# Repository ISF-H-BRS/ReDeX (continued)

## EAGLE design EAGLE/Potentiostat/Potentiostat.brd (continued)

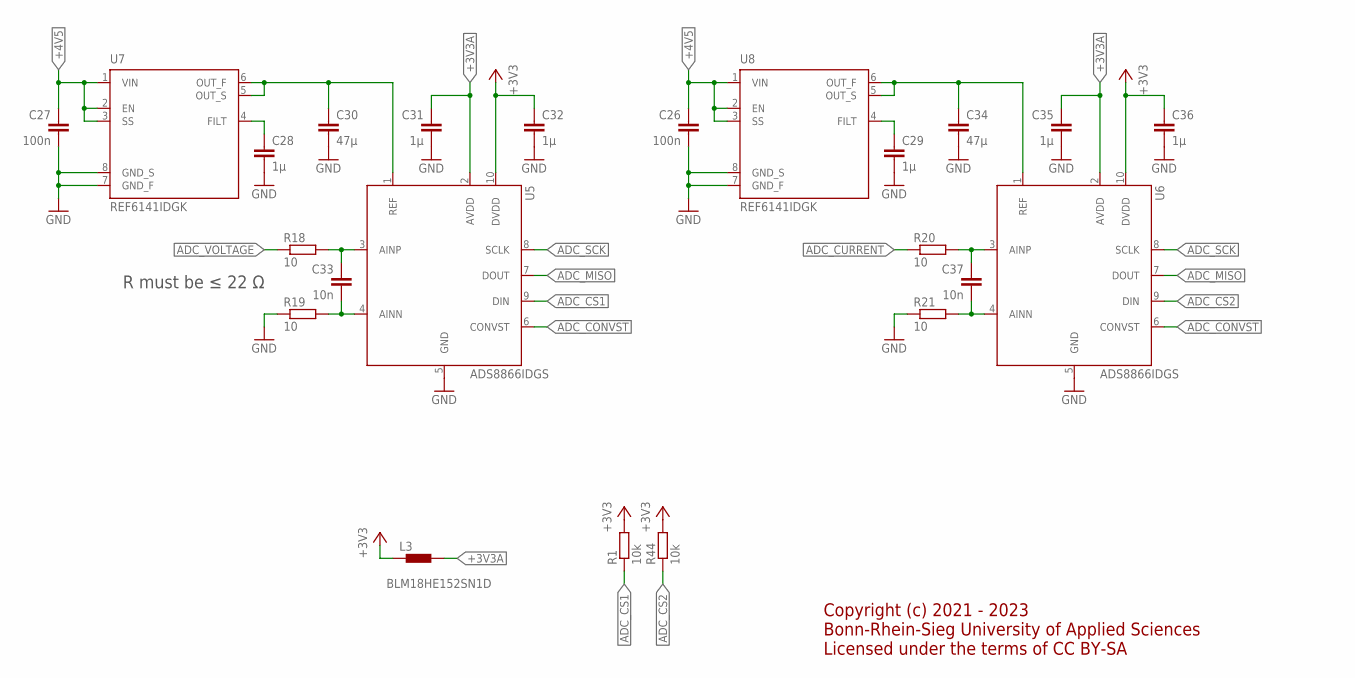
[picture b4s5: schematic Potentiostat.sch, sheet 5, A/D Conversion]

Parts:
C26, C27: 100n; C0603
C28, C29, C31, C32, C35, C36: 1µ; C0603
C30, C34: 47µ; C0805
C33, C37: 10n; C0603
L3: BLM18HE152SN1D; 0603
R1, R44: 10k; R0603
R18, R19, R20, R21: 10; R0603
U5, U6: ADS8866IDGS; MSOP10
U7, U8: REF6141IDGK; VSSOP8

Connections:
+3V3: C32.1, C36.1, L3.2, R1.2, R44.2, U5.10 (DVDD), U6.10 (DVDD); also elsewhere on the board
+3V3A: C31.1, C35.1, L3.1, U5.2 (AVDD), U6.2 (AVDD)
+4V5: C26.1, C27.1, U7.1 (VIN), U7.2 (EN), U7.3 (SS), U8.1 (VIN), U8.2 (EN), U8.3 (SS); also elsewhere on the board
ADC_CONVST: U5.6 (CONVST), U6.6 (CONVST); also elsewhere on the board
ADC_CS1: R1.1, U5.9 (DIN); also elsewhere on the board
ADC_CS2: R44.1, U6.9 (DIN); also elsewhere on the board
ADC_CURRENT: R20.1; also elsewhere on the board
ADC_MISO: U5.7 (DOUT), U6.7 (DOUT); also elsewhere on the board
ADC_SCK: U5.8 (SCLK), U6.8 (SCLK); also elsewhere on the board
ADC_VOLTAGE: R18.1; also elsewhere on the board
GND: C26.2, C27.2, C28.2, C29.2, C30.2, C31.2, C32.2, C34.2, C35.2, C36.2, R19.1, R21.1, U5.5 (GND), U6.5 (GND), U7.7 (GND_F), U7.8 (GND_S), U8.7 (GND_F), U8.8 (GND_S); also elsewhere on the board
unnamed: C28.1, U7.4 (FILT)
unnamed: C30.1, U5.1 (REF), U7.5 (OUT_S), U7.6 (OUT_F)
unnamed: C33.1, R18.2, U5.3 (AINP)
unnamed: C29.1, U8.4 (FILT)
unnamed: C34.1, U6.1 (REF), U8.5 (OUT_S), U8.6 (OUT_F)
unnamed: C33.2, R19.2, U5.4 (AINN)
unnamed: C37.1, R20.2, U6.3 (AINP)
unnamed: C37.2, R21.2, U6.4 (AINN)

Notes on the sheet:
R must be ≤ 22 Ω
Copyright (c) 2021 - 2023 Bonn-Rhein-Sieg University of Applied Sciences Licensed under the terms of CC BY-SA

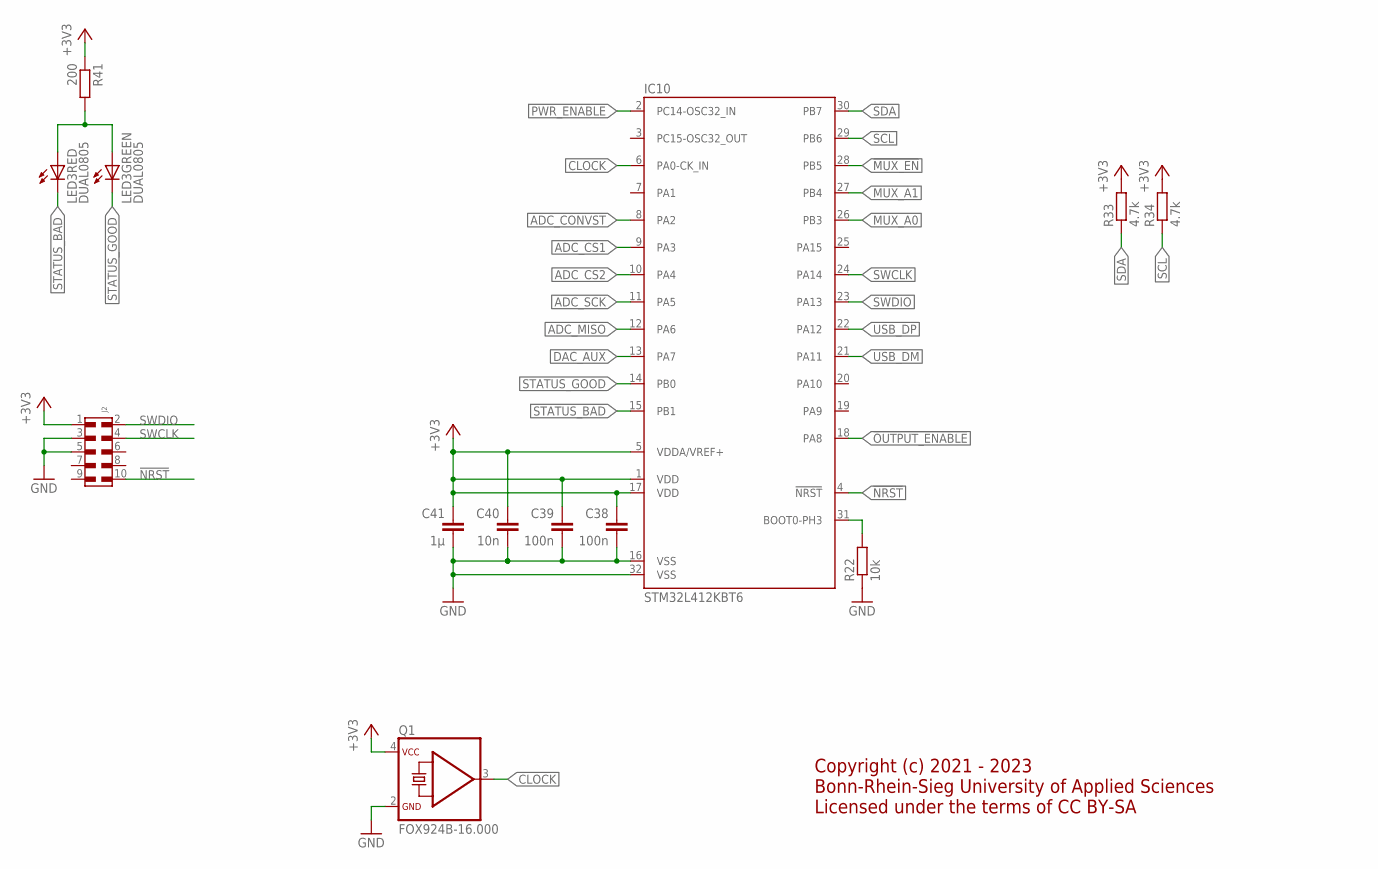
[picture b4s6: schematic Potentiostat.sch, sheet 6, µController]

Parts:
C38, C39: 100n; C0603
C40: 10n; C0603
C41: 1µ; C0603
IC10: STM32L412KBT6; LQFP32
J2: 6210XX21021_62101021021; 62101021021
LED3: DUAL0805; CHIPLEDX2
Q1: FOX924B-16.000; FOX924B
R22: 10k; R0603
R33, R34: 4.7k; R0603
R41: 200; R0603

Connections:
!MUX_EN: IC10.28 (PB5); also elsewhere on the board
!NRST: IC10.4 (!NRST), J2.10
!OUTPUT_ENABLE: IC10.18 (PA8); also elsewhere on the board
+3V3: C38.1, C39.1, C40.1, C41.1, IC10.1 (VDD), IC10.5 (VDDA/VREF+), IC10.17 (VDD), J2.1, Q1.4 (VCC), R33.2, R34.2, R41.1; also elsewhere on the board
ADC_CONVST: IC10.8 (PA2); also elsewhere on the board
ADC_CS1: IC10.9 (PA3); also elsewhere on the board
ADC_CS2: IC10.10 (PA4); also elsewhere on the board
ADC_MISO: IC10.12 (PA6); also elsewhere on the board
ADC_SCK: IC10.11 (PA5); also elsewhere on the board
CLOCK: IC10.6 (PA0-CK_IN), Q1.3 (OUT)
DAC_AUX: IC10.13 (PA7); also elsewhere on the board
GND: C38.2, C39.2, C40.2, C41.2, IC10.16 (VSS), IC10.32 (VSS), J2.3, J2.5, Q1.2 (GND), R22.1; also elsewhere on the board
MUX_A0: IC10.26 (PB3); also elsewhere on the board
MUX_A1: IC10.27 (PB4); also elsewhere on the board
unnamed: IC10.31 (BOOT0-PH3), R22.2
unnamed: LED3.A1 (A), LED3.A2 (A), R41.2
PWR_ENABLE: IC10.2 (PC14-OSC32_IN); also elsewhere on the board
SCL: IC10.29 (PB6), R34.1; also elsewhere on the board
SDA: IC10.30 (PB7), R33.1; also elsewhere on the board
STATUS_BAD: IC10.15 (PB1), LED3.C1 (C)
STATUS_GOOD: IC10.14 (PB0), LED3.C2 (C)
SWCLK: IC10.24 (PA14), J2.4
SWDIO: IC10.23 (PA13), J2.2
USB_DM: IC10.21 (PA11); also elsewhere on the board
USB_DP: IC10.22 (PA12); also elsewhere on the board

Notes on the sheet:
Copyright (c) 2021 - 2023 Bonn-Rhein-Sieg University of Applied Sciences Licensed under the terms of CC BY-SA

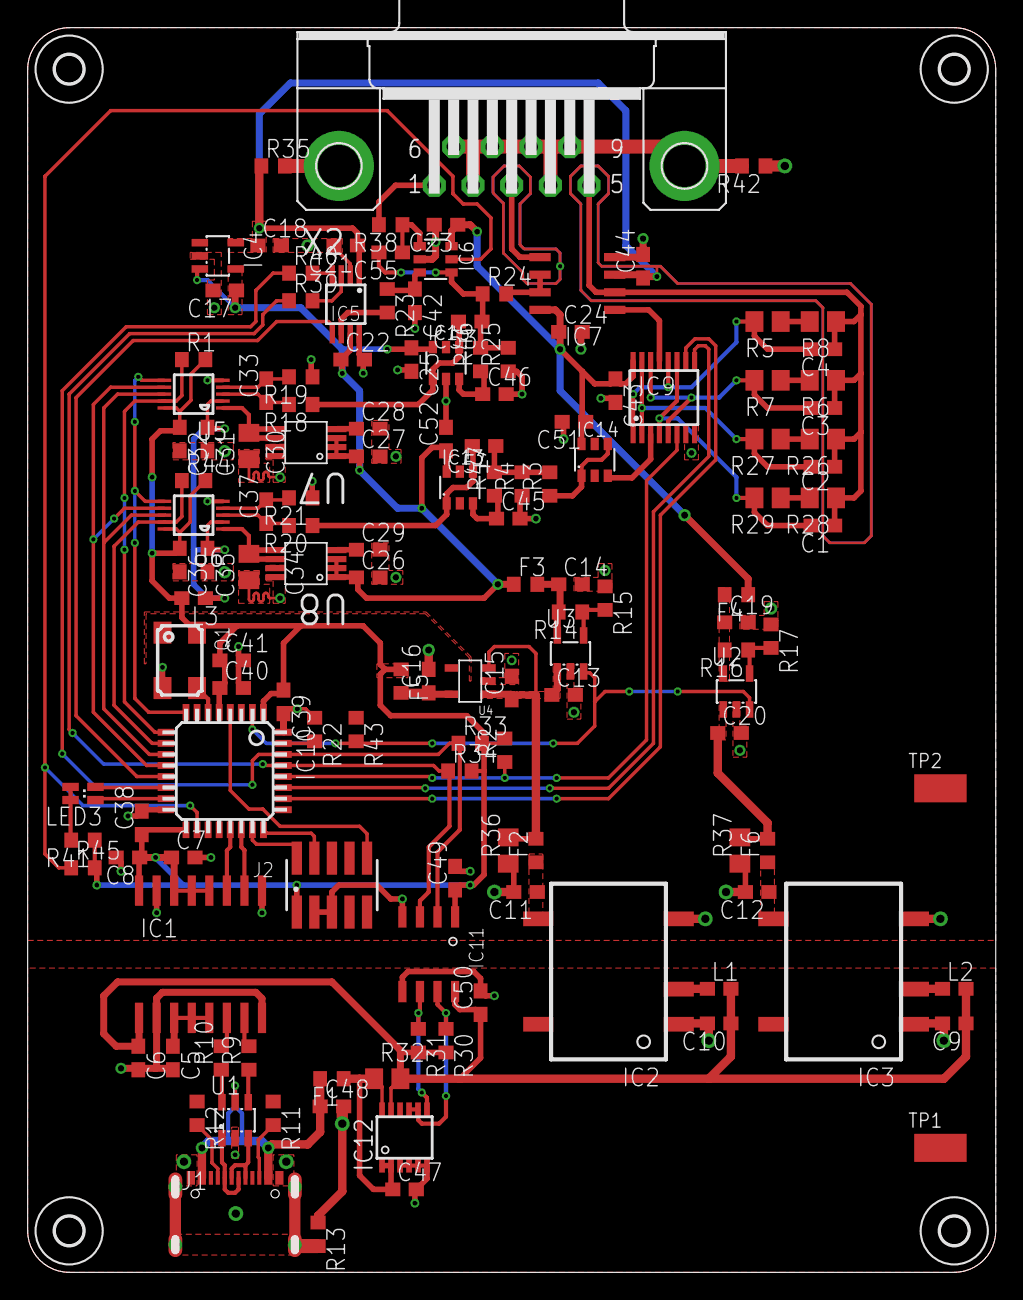
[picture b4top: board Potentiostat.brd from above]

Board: 2 copper layers, 69.4 x 89.4 mm, 144 parts (0 on the bottom side), 92 nets.

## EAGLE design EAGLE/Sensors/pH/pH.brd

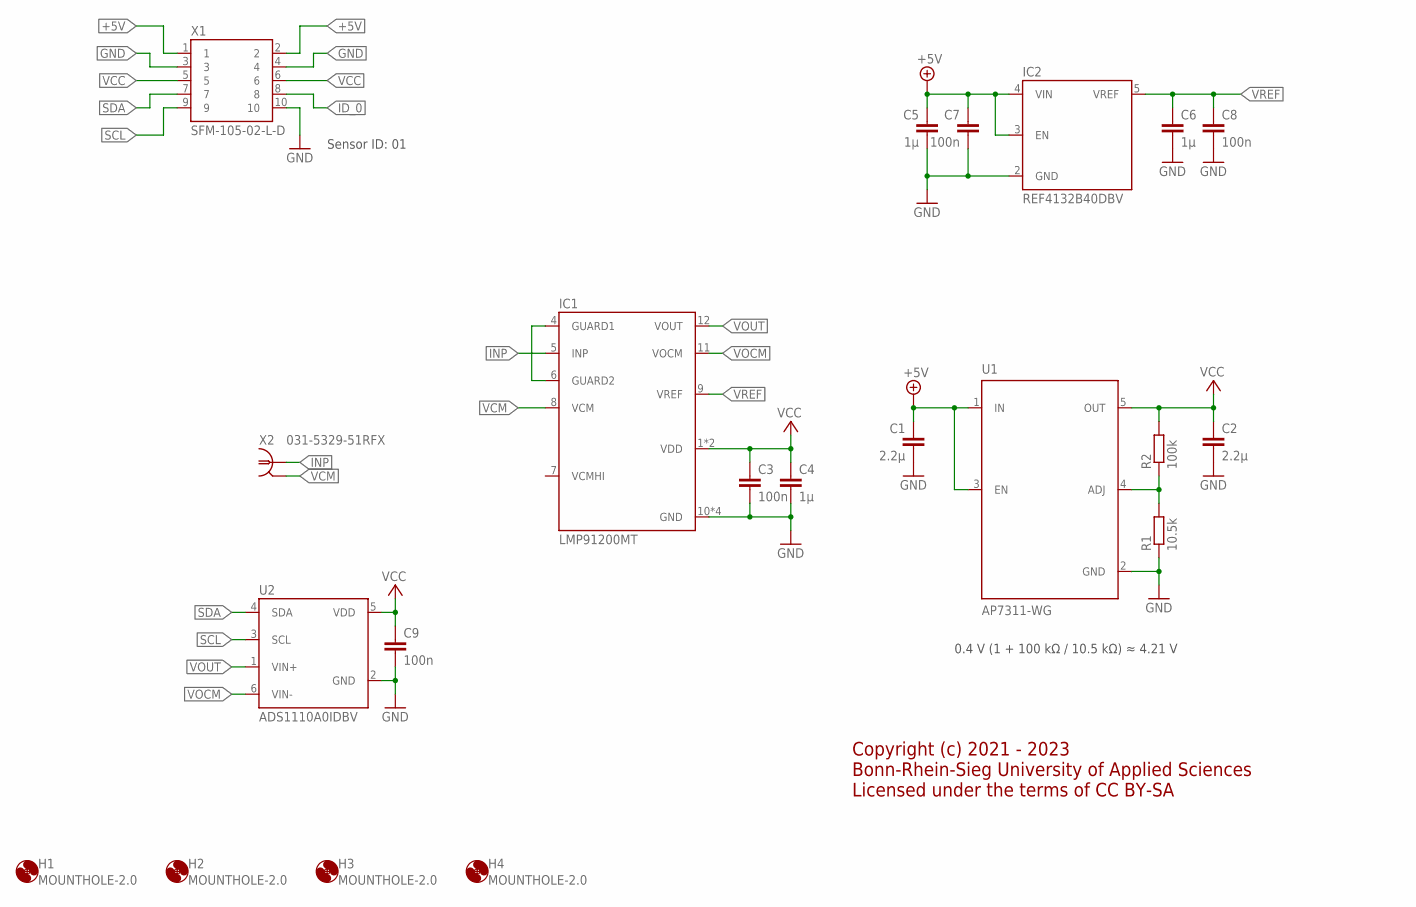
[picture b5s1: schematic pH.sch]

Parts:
C1, C2: 2.2µ; C0603
C3, C7, C8, C9: 100n; C0603
C4, C5, C6: 1µ; C0603
H1, H2, H3, H4: MOUNTHOLE-2.0; 2.0
IC1: LMP91200MT; TSSOP16
IC2: REF4132B40DBV; SOT23-5
R1: 10.5k; R0603
R2: 100k; R0603
U1: AP7311-WG; SOT-23
U2: ADS1110A0IDBV; SOT23-6
X1: SFM-105-02-L-D; SAMTEC-SFM-105-02-L-D
X2: 031-5329-51RFX

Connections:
+5V: C1.1, C5.1, C7.1, IC2.3 (EN), IC2.4 (VIN), U1.1 (IN), U1.3 (EN), X1.1, X1.2
GND: C1.2, C2.2, C3.2, C4.2, C5.2, C6.2, C7.2, C8.2, C9.2, IC1.10 (GND), IC1.13 (GND), IC1.15 (GND), IC1.16 (GND), IC2.2 (GND), R1.1, U1.2 (GND), U2.2 (GND), X1.3, X1.4, X1.10
ID_0: X1.8
INP: IC1.5 (INP), X2.1
unnamed: IC1.4 (GUARD1), IC1.6 (GUARD2)
unnamed: R1.2, R2.1, U1.4 (ADJ)
SCL: U2.3 (SCL), X1.9
SDA: U2.4 (SDA), X1.7
VCC: C2.1, C3.1, C4.1, C9.1, IC1.1 (VDD), IC1.14 (VDD), R2.2, U1.5 (OUT), U2.5 (VDD), X1.5, X1.6
VCM: IC1.8 (VCM), X2.2, X2.3 (2), X2.4 (2), X2.5 (2)
VOCM: IC1.11 (VOCM), U2.6 (VIN-)
VOUT: IC1.12 (VOUT), U2.1 (VIN+)
VREF: C6.1, C8.1, IC1.9 (VREF), IC2.5 (VREF)

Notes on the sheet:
0.4 V (1 + 100 kΩ / 10.5 kΩ) ≈ 4.21 V
Sensor ID: 01
Copyright (c) 2021 - 2023 Bonn-Rhein-Sieg University of Applied Sciences Licensed under the terms of CC BY-SA

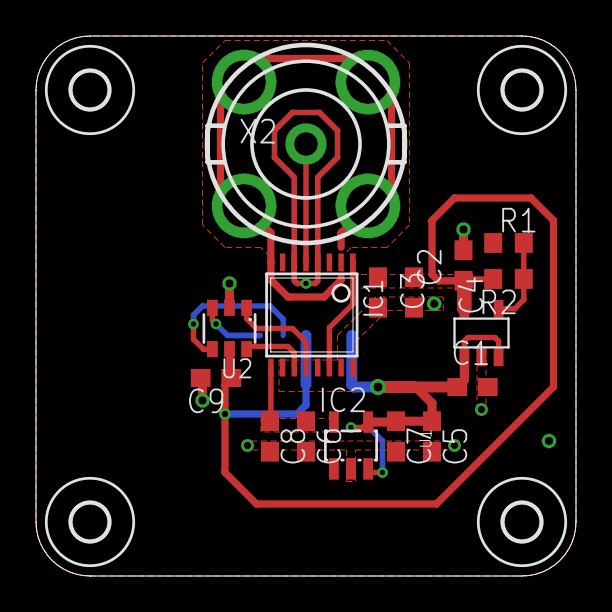
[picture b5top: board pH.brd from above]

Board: 2 copper layers, 30.0 x 30.0 mm, 21 parts (1 on the bottom side), 12 nets.

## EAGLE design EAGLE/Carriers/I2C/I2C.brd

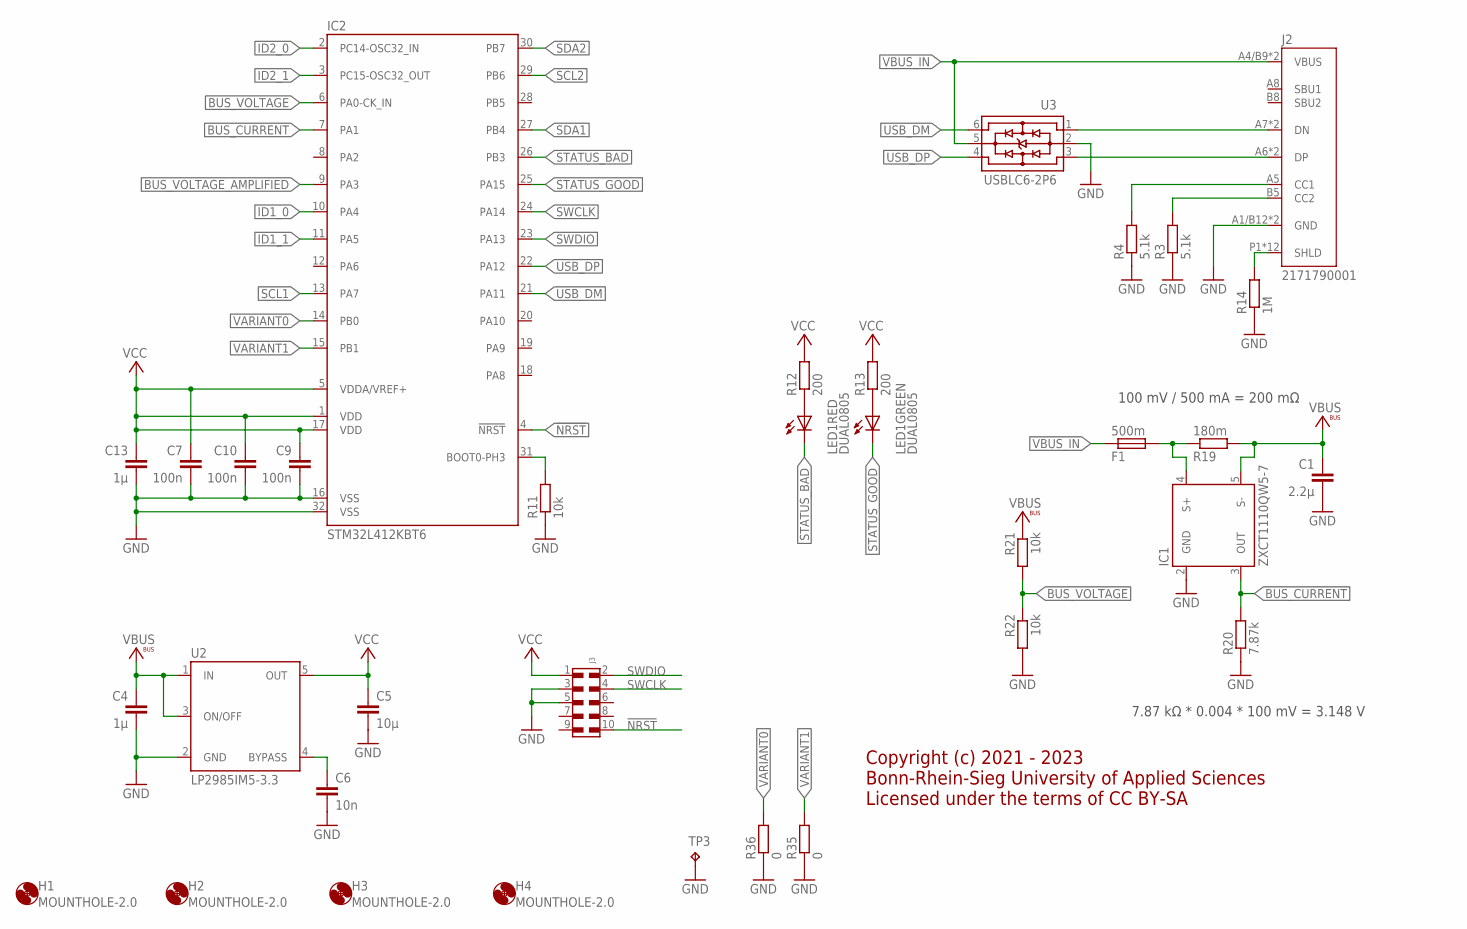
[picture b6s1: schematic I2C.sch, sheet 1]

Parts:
C1: 2.2µ; C0805
C4: 1µ; C0805
C5: 10µ; C0603
C6: 10n; C0603
C7, C9, C10: 100n; C0603
C13: 1µ; C0603
F1: 500m; R0603
H1, H2, H3, H4: MOUNTHOLE-2.0; 2.0
IC1: ZXCT1110QW5-7; SOT23-5L
IC2: STM32L412KBT6; LQFP32
J2: 2171790001; 2171790001_MOL
J3: 6210XX21021_62101021021; 62101021021
LED1: DUAL0805; CHIPLEDX2
R3, R4: 5.1k; R0603
R11, R21, R22: 10k; R0603
R12, R13: 200; R0603
R14: 1M; R0603
R19: 180m; R0805
R20: 7.87k; R0603
R35, R36: 0; R0603
TP3: TP3.8X2.03; 3.8X2.03
U2: LP2985IM5-3.3; SOT23-5
U3: USBLC6-2P6; SOT-666

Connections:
!NRST: IC2.4 (!NRST), J3.10
BUS_CURRENT: IC1.3 (OUT), IC2.7 (PA1), R20.2
BUS_VOLTAGE: IC2.6 (PA0-CK_IN), R21.2, R22.1
BUS_VOLTAGE_AMPLIFIED: IC2.9 (PA3)
GND: C1.2, C4.2, C5.2, C6.2, C7.2, C9.2, C10.2, C13.2, IC1.2 (GND), IC2.16 (VSS), IC2.32 (VSS), J2.A1/B12 (GND), J2.B1/A12 (GND), J3.3, J3.5, R3.1, R4.1, R11.1, R14.1, R20.1, R22.2, R35.1, R36.1, TP3.TP, U2.2 (GND), U3.2; also elsewhere on the board
ID1_0: IC2.10 (PA4); also elsewhere on the board
ID1_1: IC2.11 (PA5); also elsewhere on the board
ID2_0: IC2.2 (PC14-OSC32_IN); also elsewhere on the board
ID2_1: IC2.3 (PC15-OSC32_OUT); also elsewhere on the board
unnamed: J2.P1 (SHLD), J2.P2 (SHLD), J2.P3 (SHLD), J2.P4 (SHLD), J2.S1 (SHLD), J2.S2 (SHLD), J2.S3 (SHLD), J2.S4 (SHLD), J2.S5 (SHLD), J2.S6 (SHLD), J2.S7 (SHLD), J2.S8 (SHLD), R14.2
unnamed: J2.A6 (DP), J2.B6 (DP), U3.3
unnamed: J2.A7 (DN), J2.B7 (DN), U3.1
unnamed: J2.B5 (CC2), R3.2
unnamed: J2.A5 (CC1), R4.2
unnamed: C6.1, U2.4 (BYPASS)
unnamed: IC2.31 (BOOT0-PH3), R11.2
unnamed: LED1.A2 (A), R13.1
unnamed: LED1.A1 (A), R12.1
unnamed: F1.2, IC1.4 (S+), R19.1
SCL1: IC2.13 (PA7); also elsewhere on the board
SCL2: IC2.29 (PB6); also elsewhere on the board
SDA1: IC2.27 (PB4); also elsewhere on the board
SDA2: IC2.30 (PB7); also elsewhere on the board
STATUS_BAD: IC2.26 (PB3), LED1.C1 (C)
STATUS_GOOD: IC2.25 (PA15), LED1.C2 (C)
SWCLK: IC2.24 (PA14), J3.4
SWDIO: IC2.23 (PA13), J3.2
USB_DM: IC2.21 (PA11), U3.6
USB_DP: IC2.22 (PA12), U3.4
VARIANT0: IC2.14 (PB0), R36.2
VARIANT1: IC2.15 (PB1), R35.2
VBUS: C1.1, C4.1, IC1.5 (S-), R19.2, R21.1, U2.1 (IN), U2.3 (ON/OFF); also elsewhere on the board
VBUS_IN: F1.1, J2.A4/B9 (VBUS), J2.B4/A9 (VBUS), U3.5
VCC: C5.1, C7.1, C9.1, C10.1, C13.1, IC2.1 (VDD), IC2.5 (VDDA/VREF+), IC2.17 (VDD), J3.1, R12.2, R13.2, U2.5 (OUT); also elsewhere on the board

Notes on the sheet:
100 mV / 500 mA = 200 mΩ
7.87 kΩ * 0.004 * 100 mV = 3.148 V
Copyright (c) 2021 - 2023 Bonn-Rhein-Sieg University of Applied Sciences Licensed under the terms of CC BY-SA

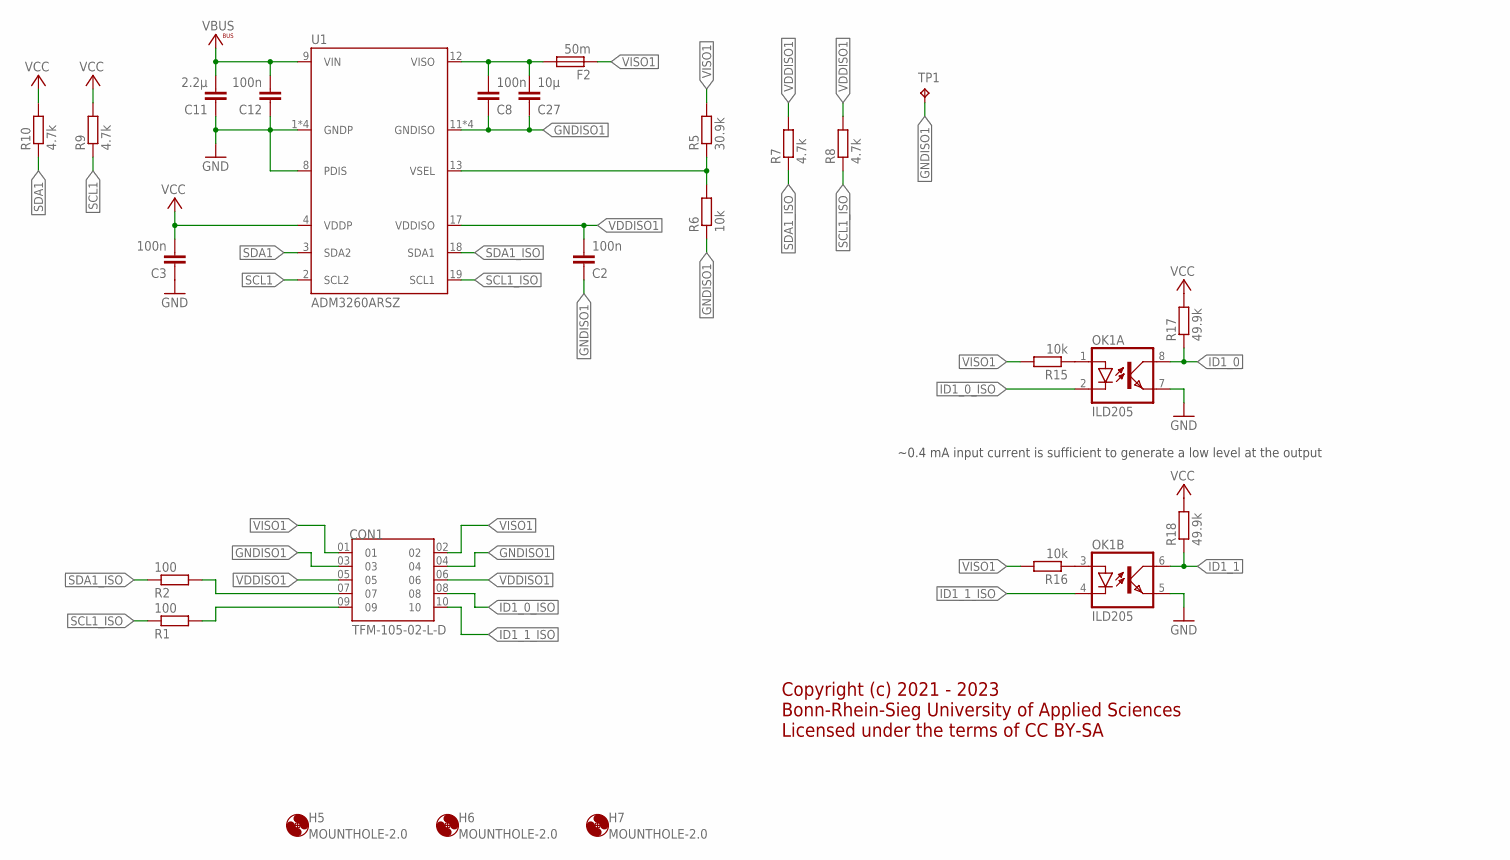
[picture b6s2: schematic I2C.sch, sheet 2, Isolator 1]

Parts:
C2, C3, C8, C12: 100n; C0603
C11: 2.2µ; C0603
C27: 10µ; C0603
CON1: TFM-105-02-L-D; SAMTEC_TFM-105-02-L-D
F2: 50m; R0603
H5, H6, H7: MOUNTHOLE-2.0; 2.0
OK1: ILD205; SOIC08
R1, R2: 100; R0603
R5: 30.9k; R0603
R6, R15, R16: 10k; R0603
R7, R8, R9, R10: 4.7k; R0603
R17, R18: 49.9k; R0603
TP1: TP3.8X2.03; 3.8X2.03
U1: ADM3260ARSZ; SSOP20

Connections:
GND: C3.1, C11.1, C12.1, OK1.5 (EMIT), OK1.7 (EMIT), U1.1 (GNDP), U1.5 (GNDP), U1.7 (GNDP), U1.8 (PDIS), U1.10 (GNDP); also elsewhere on the board
GNDISO1: C2.1, C8.1, C27.1, CON1.03, CON1.04, R6.1, TP1.TP, U1.11 (GNDISO), U1.14 (GNDISO), U1.16 (GNDISO), U1.20 (GNDISO)
ID1_0: OK1.8 (COL), R17.1; also elsewhere on the board
ID1_0_ISO: CON1.08, OK1.2 (C)
ID1_1: OK1.6 (COL), R18.1; also elsewhere on the board
ID1_1_ISO: CON1.10, OK1.4 (C)
unnamed: CON1.09, R1.2
unnamed: R5.1, R6.2, U1.13 (VSEL)
unnamed: CON1.07, R2.2
unnamed: OK1.3 (A), R16.1
unnamed: OK1.1 (A), R15.1
unnamed: C8.2, C27.2, F2.2, U1.12 (VISO)
SCL1: R9.1, U1.2 (SCL2); also elsewhere on the board
SCL1_ISO: R1.1, R8.1, U1.19 (SCL1)
SDA1: R10.1, U1.3 (SDA2); also elsewhere on the board
SDA1_ISO: R2.1, R7.1, U1.18 (SDA1)
VBUS: C11.2, C12.2, U1.9 (VIN); also elsewhere on the board
VCC: C3.2, R9.2, R10.2, R17.2, R18.2, U1.4 (VDDP); also elsewhere on the board
VDDISO1: C2.2, CON1.05, CON1.06, R7.2, R8.2, U1.17 (VDDISO)
VISO1: CON1.01, CON1.02, F2.1, R5.2, R15.2, R16.2

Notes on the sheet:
~0.4 mA input current is sufficient to generate a low level at the output
Copyright (c) 2021 - 2023 Bonn-Rhein-Sieg University of Applied Sciences Licensed under the terms of CC BY-SA

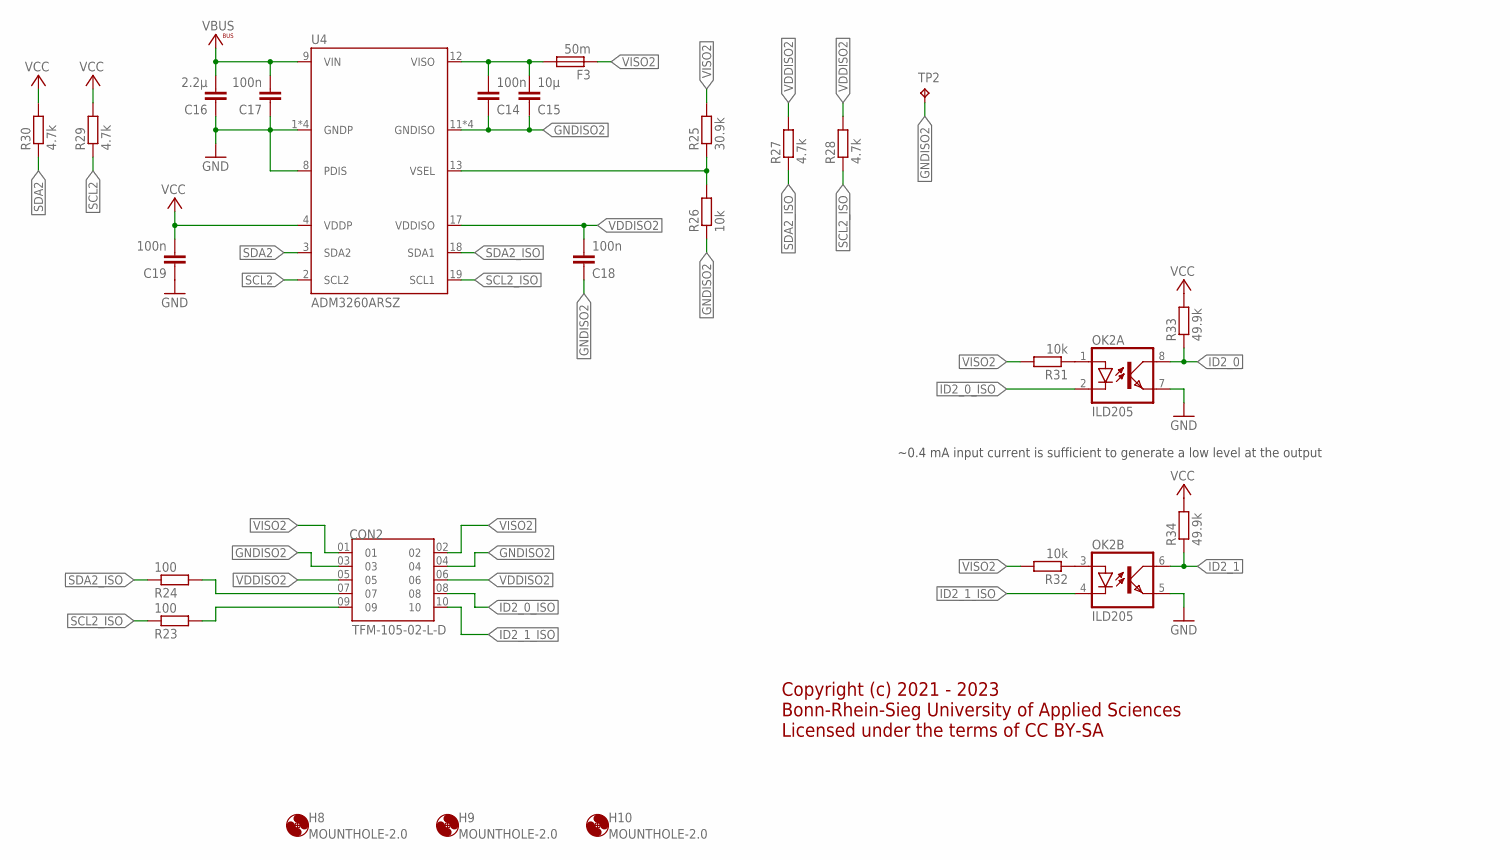
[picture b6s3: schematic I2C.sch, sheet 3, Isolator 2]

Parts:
C14, C17, C18, C19: 100n; C0603
C15: 10µ; C0603
C16: 2.2µ; C0603
CON2: TFM-105-02-L-D; SAMTEC_TFM-105-02-L-D
F3: 50m; R0603
H8, H9, H10: MOUNTHOLE-2.0; 2.0
OK2: ILD205; SOIC08
R23, R24: 100; R0603
R25: 30.9k; R0603
R26, R31, R32: 10k; R0603
R27, R28, R29, R30: 4.7k; R0603
R33, R34: 49.9k; R0603
TP2: TP3.8X2.03; 3.8X2.03
U4: ADM3260ARSZ; SSOP20

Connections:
GND: C16.1, C17.1, C19.1, OK2.5 (EMIT), OK2.7 (EMIT), U4.1 (GNDP), U4.5 (GNDP), U4.7 (GNDP), U4.8 (PDIS), U4.10 (GNDP); also elsewhere on the board
GNDISO2: C14.1, C15.1, C18.1, CON2.03, CON2.04, R26.1, TP2.TP, U4.11 (GNDISO), U4.14 (GNDISO), U4.16 (GNDISO), U4.20 (GNDISO)
ID2_0: OK2.8 (COL), R33.1; also elsewhere on the board
ID2_0_ISO: CON2.08, OK2.2 (C)
ID2_1: OK2.6 (COL), R34.1; also elsewhere on the board
ID2_1_ISO: CON2.10, OK2.4 (C)
unnamed: R25.1, R26.2, U4.13 (VSEL)
unnamed: CON2.09, R23.2
unnamed: CON2.07, R24.2
unnamed: OK2.3 (A), R32.1
unnamed: OK2.1 (A), R31.1
unnamed: C14.2, C15.2, F3.2, U4.12 (VISO)
SCL2: R29.1, U4.2 (SCL2); also elsewhere on the board
SCL2_ISO: R23.1, R28.1, U4.19 (SCL1)
SDA2: R30.1, U4.3 (SDA2); also elsewhere on the board
SDA2_ISO: R24.1, R27.1, U4.18 (SDA1)
VBUS: C16.2, C17.2, U4.9 (VIN); also elsewhere on the board
VCC: C19.2, R29.2, R30.2, R33.2, R34.2, U4.4 (VDDP); also elsewhere on the board
VDDISO2: C18.2, CON2.05, CON2.06, R27.2, R28.2, U4.17 (VDDISO)
VISO2: CON2.01, CON2.02, F3.1, R25.2, R31.2, R32.2

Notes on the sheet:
~0.4 mA input current is sufficient to generate a low level at the output
Copyright (c) 2021 - 2023 Bonn-Rhein-Sieg University of Applied Sciences Licensed under the terms of CC BY-SA

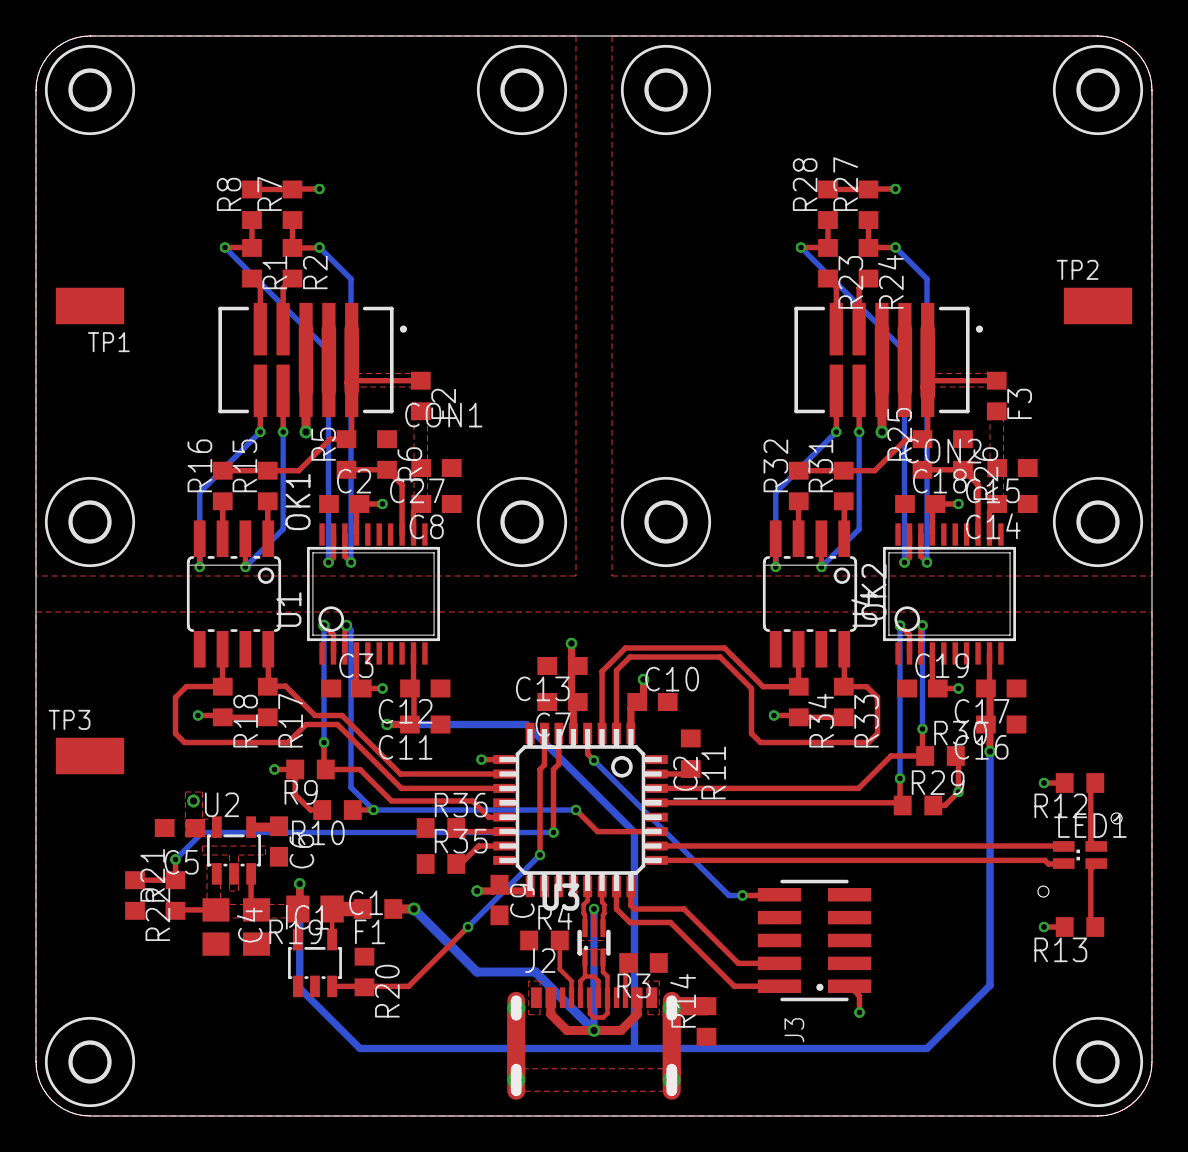
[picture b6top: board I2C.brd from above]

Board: 2 copper layers, 61.4 x 59.4 mm, 85 parts (0 on the bottom side), 59 nets.

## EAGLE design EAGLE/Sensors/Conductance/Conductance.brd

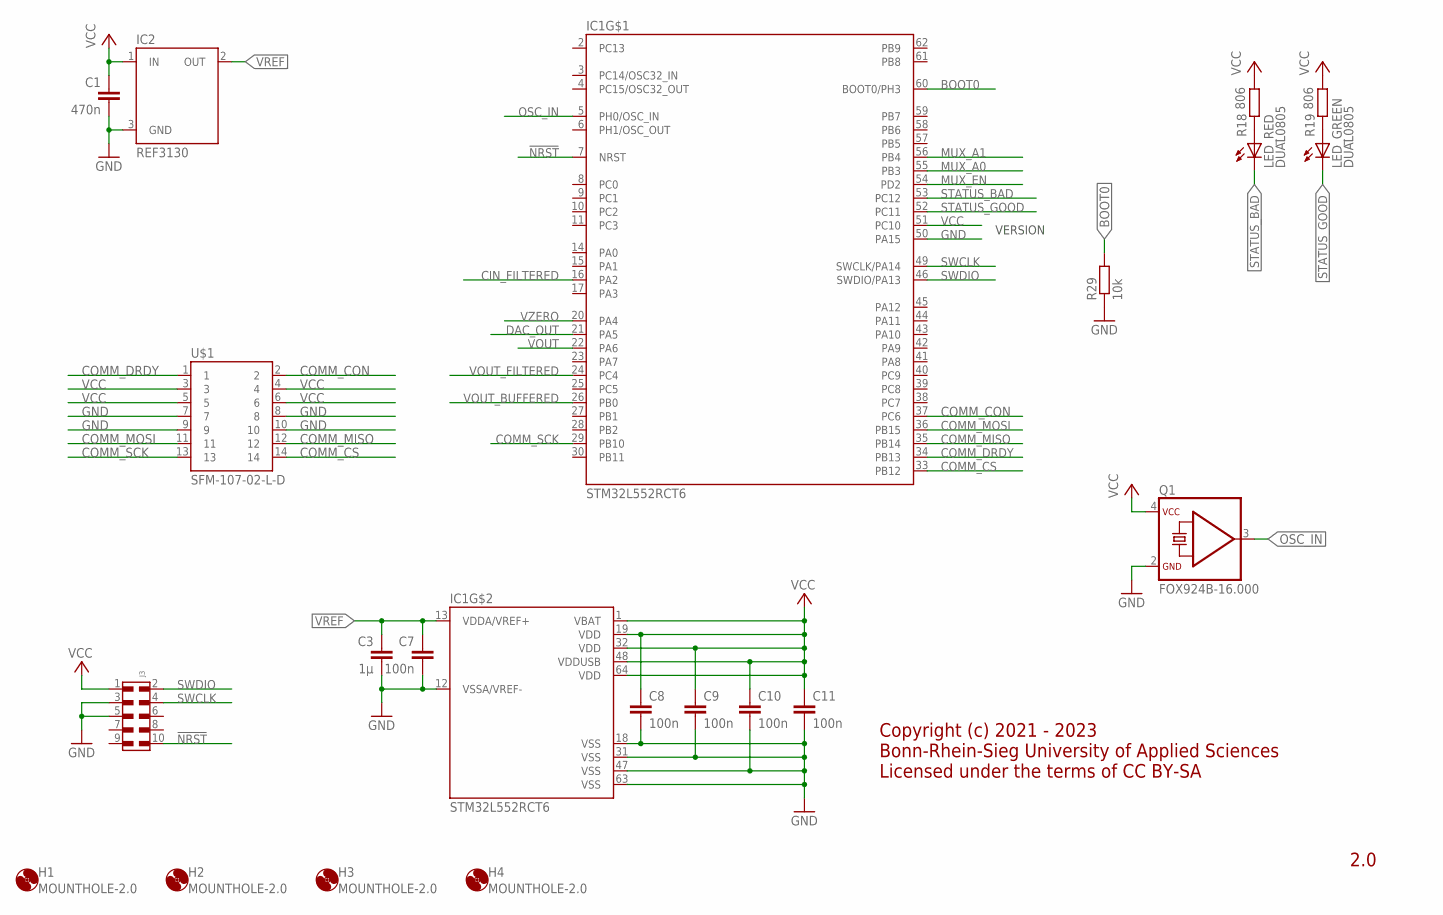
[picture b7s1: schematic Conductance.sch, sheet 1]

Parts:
C1: 470n; C0603
C3: 1µ; C0603
C7, C8, C9, C10, C11: 100n; C0603
H1, H2, H3, H4: MOUNTHOLE-2.0; 2.0
IC1: STM32L552RCT6; LQFP64
IC2: REF3130; SOT23
J3: 6210XX21021_62101021021; 62101021021
LED_: DUAL0805; CHIPLEDX2
Q1: FOX924B-16.000; FOX924B
R18, R19: 806; R0603
R29: 10k; R0603
U$1: SFM-107-02-L-D; SAMTEC-SFM-107-02-L-D

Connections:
!NRST: IC1.7 (NRST), J3.10
BOOT0: IC1.60 (BOOT0/PH3), R29.2
CIN_FILTERED: IC1.16 (PA2); also elsewhere on the board
COMM_CON: IC1.37 (PC6), U$1.2
COMM_CS: IC1.33 (PB12), U$1.14
COMM_DRDY: IC1.34 (PB13), U$1.1
COMM_MISO: IC1.35 (PB14), U$1.12
COMM_MOSI: IC1.36 (PB15), U$1.11
COMM_SCK: IC1.29 (PB10), U$1.13
DAC_OUT: IC1.21 (PA5); also elsewhere on the board
GND: C1.2, C3.2, C7.2, C8.2, C9.2, C10.2, C11.2, IC1.12 (VSSA/VREF-), IC1.18 (VSS), IC1.31 (VSS), IC1.47 (VSS), IC1.50 (PA15), IC1.63 (VSS), IC2.3 (GND), J3.3, J3.5, Q1.2 (GND), R29.1, U$1.7, U$1.8, U$1.9, U$1.10; also elsewhere on the board
MUX_A0: IC1.55 (PB3); also elsewhere on the board
MUX_A1: IC1.56 (PB4); also elsewhere on the board
MUX_EN: IC1.54 (PD2); also elsewhere on the board
unnamed: LED_.A1 (A), R18.1
unnamed: LED_.A2 (A), R19.1
OSC_IN: IC1.5 (PH0/OSC_IN), Q1.3 (OUT)
STATUS_BAD: IC1.53 (PC12), LED_.C1 (C)
STATUS_GOOD: IC1.52 (PC11), LED_.C2 (C)
SWCLK: IC1.49 (SWCLK/PA14), J3.4
SWDIO: IC1.46 (SWDIO/PA13), J3.2
VCC: C1.1, C8.1, C9.1, C10.1, C11.1, IC1.1 (VBAT), IC1.19 (VDD), IC1.32 (VDD), IC1.48 (VDDUSB), IC1.51 (PC10), IC1.64 (VDD), IC2.1 (IN), J3.1, Q1.4 (VCC), R18.2, R19.2, U$1.3, U$1.4, U$1.5, U$1.6; also elsewhere on the board
VOUT: IC1.22 (PA6); also elsewhere on the board
VOUT_BUFFERED: IC1.26 (PB0); also elsewhere on the board
VOUT_FILTERED: IC1.24 (PC4); also elsewhere on the board
VREF: C3.1, C7.1, IC1.13 (VDDA/VREF+), IC2.2 (OUT); also elsewhere on the board
VZERO: IC1.20 (PA4); also elsewhere on the board

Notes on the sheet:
2.0
VERSION
Copyright (c) 2021 - 2023 Bonn-Rhein-Sieg University of Applied Sciences Licensed under the terms of CC BY-SA

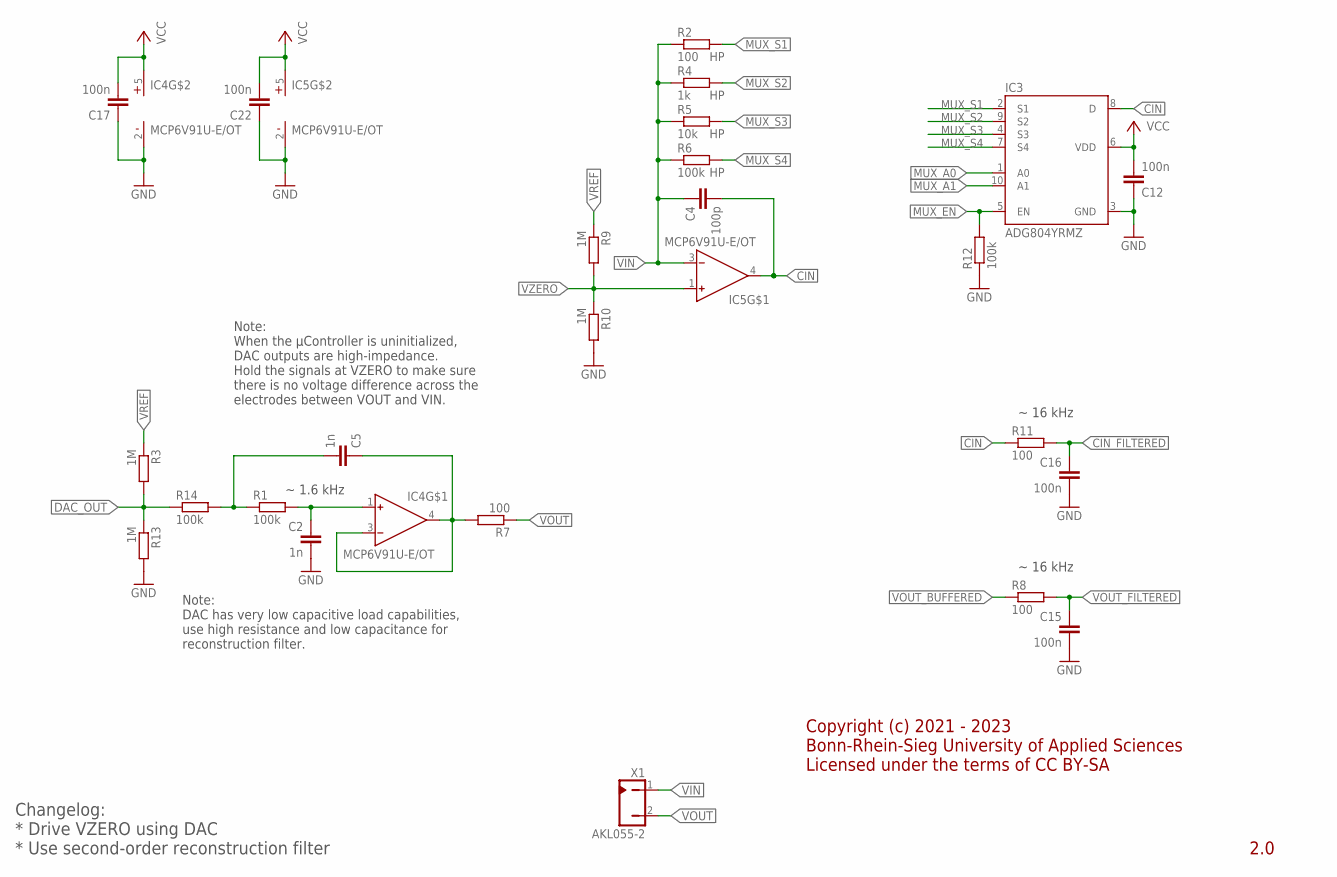
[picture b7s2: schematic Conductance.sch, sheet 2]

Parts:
C2, C5: 1n; C0603
C4: 100p; C0603
C12, C15, C16, C17, C22: 100n; C0603
IC3: ADG804YRMZ; MSOP10
IC4, IC5: MCP6V91U-E/OT; SOT23-5
R1, R6, R12, R14: 100k; R0603
R2, R7, R8, R11: 100; R0603
R3, R9, R10, R13: 1M; R0603
R4: 1k; R0603
R5: 10k; R0603
X1: AKL055-2

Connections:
CIN: C4.2, IC3.8 (D), IC5.4 (OUT), R11.1
CIN_FILTERED: C16.1, R11.2; also elsewhere on the board
DAC_OUT: R3.2, R13.1, R14.1; also elsewhere on the board
GND: C2.2, C12.1, C15.2, C16.2, C17.1, C22.1, IC3.3 (GND), IC4.2 (VSS), IC5.2 (VSS), R10.2, R12.1, R13.2; also elsewhere on the board
MUX_A0: IC3.1 (A0); also elsewhere on the board
MUX_A1: IC3.10 (A1); also elsewhere on the board
MUX_EN: IC3.5 (EN), R12.2; also elsewhere on the board
MUX_S1: IC3.2 (S1), R2.2
MUX_S2: IC3.9 (S2), R4.2
MUX_S3: IC3.4 (S3), R5.2
MUX_S4: IC3.7 (S4), R6.2
unnamed: C5.2, R1.1, R14.2
unnamed: C2.1, IC4.1 (IN+), R1.2
unnamed: C5.1, IC4.3 (IN-), IC4.4 (OUT), R7.2
VCC: C12.2, C17.2, C22.2, IC3.6 (VDD), IC4.5 (VDD), IC5.5 (VDD); also elsewhere on the board
VIN: C4.1, IC5.3 (IN-), R2.1, R4.1, R5.1, R6.1, X1.1
VOUT: R7.1, X1.2 (4); also elsewhere on the board
VOUT_BUFFERED: R8.1; also elsewhere on the board
VOUT_FILTERED: C15.1, R8.2; also elsewhere on the board
VREF: R3.1, R9.1; also elsewhere on the board
VZERO: IC5.1 (IN+), R9.2, R10.1; also elsewhere on the board

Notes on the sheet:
Note: DAC has very low capacitive load capabilities, use high resistance and low capacitance for reconstruction filter.
Note: When the µController is uninitialized, DAC outputs are high-impedance. Hold the signals at VZERO to make sure there is no voltage difference across the electrodes between VOUT and VIN.
2.0
Changelog: * Drive VZERO using DAC * Use second-order reconstruction filter
~ 1.6 kHz
~ 16 kHz
Copyright (c) 2021 - 2023 Bonn-Rhein-Sieg University of Applied Sciences Licensed under the terms of CC BY-SA

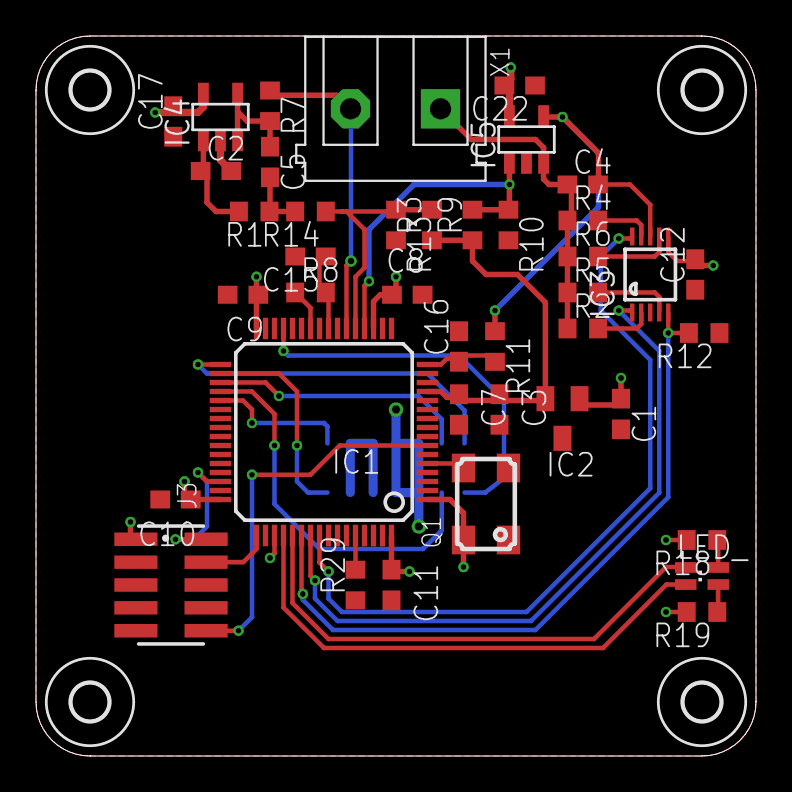
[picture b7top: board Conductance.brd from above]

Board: 2 copper layers, 40.0 x 40.0 mm, 46 parts (1 on the bottom side), 36 nets.
